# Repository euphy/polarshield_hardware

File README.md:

Polarshield Hardware
====================

This is the source for the Polarshield hardware, in EAGLE format.  
I have also included the last set of generated Gerber files that were used to make
the most recent batch of PCBs. These can be purchased through polargraph.bigcartel.com.

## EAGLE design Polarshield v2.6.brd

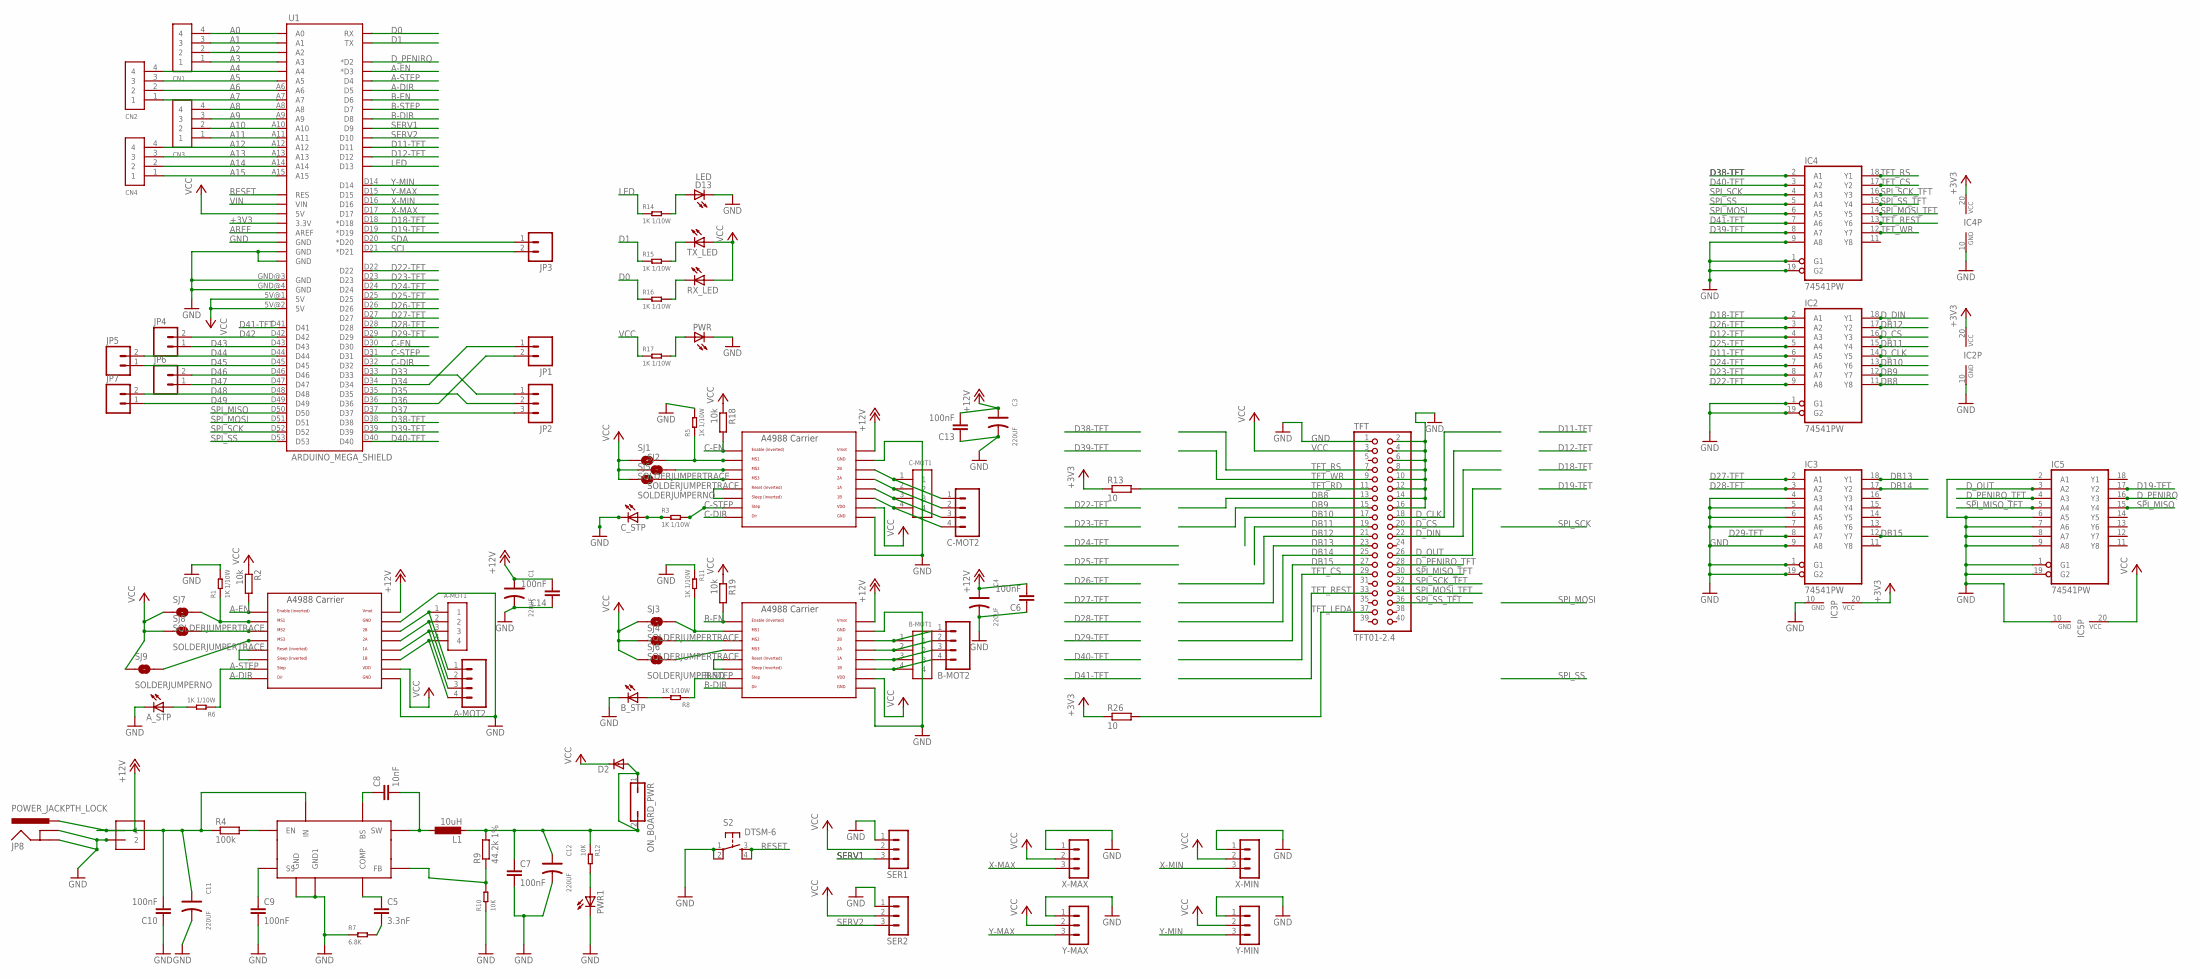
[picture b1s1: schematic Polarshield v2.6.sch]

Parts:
A-MOT1: 1X4-BIG; 1X04-BIG
A-MOT2: M04SCREW; SCREWTERMINAL-3.5MM-4
A_STP: LEDCHIP-LED0805; CHIP-LED0805
B-MOT1: 1X4-BIG; 1X04-BIG
B-MOT2: M04SCREW; SCREWTERMINAL-3.5MM-4
B_STP: LEDCHIP-LED0805; CHIP-LED0805
C1, C3, C4, C11, C12: 220UF; ELECTRO-SMD-C-6MM
C5: 3.3nF; C0402K
C6, C7, C9, C10, C13, C14: 100nF; C0402K
C8: 10nF; C0402K
C-MOT1: 1X4-BIG; 1X04-BIG
C-MOT2: M04SCREW; SCREWTERMINAL-3.5MM-4
CN1, CN2, CN3, CN4: 1X4-CLEANBIG; 1X04-CLEANBIG
C_STP: LEDCHIP-LED0805; CHIP-LED0805
D2: DIODE-DO214BA; DO214BA
D13: LED; CHIP-LED0805
IC1: MP2307; SOIC8
IC2, IC3, IC4, IC5: 74541PW; TSSOP20
J1: 1X2-3.5MM
JP1, JP3, JP4, JP5, JP6, JP7: M021X02_NO_SILK; 1X02_NO_SILK
JP2: M031X03_NO_SILK; 1X03_NO_SILK
JP8: POWER_JACKPTH_LOCK; POWER_JACK_PTH_LOCK
L1: 10uH; PIS2816
ON_BOARD_PWR: JP1Q; JP1
PWR, PWR1: LEDCHIP-LED0805; CHIP-LED0805
R1, R3, R5, R6, R8, R11, R14, R15, R16, R17: 1K 1/10W; R0603
R2, R18, R19: 10k; R0402
R4: 100k; R0603
R7: 6.8K; R0603
R9: 44.2k 1%; R0603
R10: 10K; R0805
R12: 10K; R0603
R13, R26: 10; R0603
RX_LED: LEDCHIP-LED0805; CHIP-LED0805
S2: DTSM-6
SER1, SER2: 3PIN-HEADER
SJ1, SJ2, SJ3, SJ4, SJ7, SJ8: SOLDERJUMPERTRACE; SJ_2S-TRACE
SJ5, SJ6, SJ9: SOLDERJUMPERNO; SJ_2S-NO
TFT: TFT01-2.4
TX_LED: LEDCHIP-LED0805; CHIP-LED0805
U1: ARDUINO_MEGA_SHIELD
U$1, U$6, U$7: A4988BREAKOUT
X-MAX: 3PIN-HEADER
X-MIN: 3PIN-HEADER
Y-MAX: 3PIN-HEADER
Y-MIN: 3PIN-HEADER

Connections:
+3V3: IC2.20 (VCC), IC3.20 (VCC), IC4.20 (VCC), R13.1, R26.1, U1.3.3V
+12V: C1.+, C3.+, C4.+, C6.2, C10.2, C11.+, C13.2, C14.2, IC1.IN, J1.1, JP8.PWR, R4.1, U$1.VMOT, U$6.VMOT, U$7.VMOT
A0: CN1.4, U1.A0
A1: CN1.3, U1.A1
A2: CN1.2, U1.A2
A3: CN1.1, U1.A3
A4: CN2.4, U1.A4
A5: CN2.3, U1.A5
A6: CN2.2, U1.A6
A7: CN2.1, U1.A7
A8: CN3.4, U1.A8
A9: CN3.3, U1.A9
A10: CN3.2, U1.A10
A11: CN3.1, U1.A11
A12: CN4.4, U1.A12
A13: CN4.3, U1.A13
A14: CN4.2, U1.A14
A15: CN4.1, U1.A15
A-DIR: U1.D5, U$1.DIR
A-EN: R2.2, U1.D3 (*D3), U$1.EN
A-STEP: R6.1, U1.D4, U$1.STEP
AREF: U1.AREF
B-DIR: U1.D8, U$7.DIR
B-EN: R19.2, U1.D6, U$7.EN
B-STEP: R8.1, U1.D7, U$7.STEP
C-DIR: U1.D32, U$6.DIR
C-EN: R18.2, U1.D30, U$6.EN
C-STEP: R3.2, U1.D31, U$6.STEP
D0: R16.1, U1.RX
D1: R15.1, U1.TX
D11-TFT: IC2.6 (A5), U1.D11
D12-TFT: IC2.4 (A3), U1.D12
D18-TFT: IC2.2 (A1), U1.D18 (*D18)
D19-TFT: IC5.17 (Y2), U1.D19 (*D19)
D22-TFT: IC2.9 (A8), U1.D22
D23-TFT: IC2.8 (A7), U1.D23
D24-TFT: IC2.7 (A6), U1.D24
D25-TFT: IC2.5 (A4), U1.D25
D26-TFT: IC2.3 (A2), U1.D26
D27-TFT: IC3.2 (A1), U1.D27
D28-TFT: IC3.3 (A2), U1.D28
D29-TFT: IC3.8 (A7), U1.D29
D33: JP2.1, U1.D33
D34: JP1.1, U1.D34
D35: JP2.2, U1.D35
D36: JP1.2, U1.D36
D37: JP2.3, U1.D37
D38-TFT: IC4.2 (A1), U1.D38
D39-TFT: IC4.8 (A7), U1.D39
D40-TFT: IC4.3 (A2), U1.D40
D41-TFT: IC4.7 (A6), U1.D41
D42: JP4.2, U1.D42
D43: JP4.1, U1.D43
D44: JP5.2, U1.D44
D45: JP5.1, U1.D45
D46: JP6.2, U1.D46
D47: JP6.1, U1.D47
D48: JP7.2, U1.D48
D49: JP7.1, U1.D49
DB8: IC2.11 (Y8), TFT.13
DB9: IC2.12 (Y7), TFT.15
DB10: IC2.13 (Y6), TFT.17
DB11: IC2.15 (Y4), TFT.19
DB12: IC2.17 (Y2), TFT.21
DB13: IC3.18 (Y1), TFT.23
DB14: IC3.17 (Y2), TFT.25
DB15: IC3.12 (Y7), TFT.27
D_CLK: IC2.14 (Y5), TFT.18
D_CS: IC2.16 (Y3), TFT.20
D_DIN: IC2.18 (Y1), TFT.22
D_OUT: IC5.3 (A2), TFT.26
D_PENIRQ: IC5.16 (Y3), U1.D2 (*D2)
D_PENIRQ_TFT: IC5.4 (A3), TFT.28
GND: A_STP.C, B_STP.C, C1.-, C3.-, C4.-, C6.1, C7.2, C9.2, C10.1, C11.-, C12.-, C13.1, C14.1, C_STP.C, D13.C, IC1.GND, IC1.GND1, IC2.1 (G1), IC2.10 (GND), IC2.19 (G2), IC3.1 (G1), IC3.4 (A3), IC3.5 (A4), IC3.6 (A5), IC3.7 (A6), IC3.9 (A8), IC3.10 (GND), IC3.19 (G2), IC4.1 (G1), IC4.9 (A8), IC4.10 (GND), IC4.19 (G2), IC5.1 (G1), IC5.2 (A1), IC5.6 (A5), IC5.7 (A6), IC5.8 (A7), IC5.9 (A8), IC5.10 (GND), IC5.19 (G2), J1.2, JP8.GND, JP8.GNDBREAK, PWR.C, PWR1.C, R1.2, R5.2, R7.1, R10.1, R11.1, S2.1, S2.2, SER1.1, SER2.1, TFT.1, TFT.2, TFT.4, TFT.6, TFT.8, TFT.10, TFT.12, TFT.14, TFT.16, U1.GND@0 (GND), U1.GND@1 (GND), U1.GND@2 (GND), U1.GND@3 (GND), U1.GND@4 (GND), U$1.GND, U$1.GND@0 (GND), U$6.GND, U$6.GND@0 (GND), U$7.GND, U$7.GND@0 (GND), X-MAX.1, X-MIN.1, Y-MAX.1, Y-MIN.1
LED: R14.1, U1.D13
unnamed: U$6.RST, U$6.SLP (SLEEP)
unnamed: PWR.A, R17.2
unnamed: R5.1, SJ1.2, U$6.MS1
unnamed: A-MOT1.1, A-MOT2.1, U$1.2B
unnamed: A-MOT1.2, A-MOT2.2, U$1.2A
unnamed: A-MOT1.3, A-MOT2.3, U$1.1A
unnamed: A-MOT1.4, A-MOT2.4, U$1.1B
unnamed: U$1.RST, U$1.SLP (SLEEP)
unnamed: R1.1, SJ7.2, U$1.MS1
unnamed: SJ2.2, U$6.MS2
unnamed: SJ8.2, U$1.MS2
unnamed: SJ5.2, U$6.MS3
unnamed: U$7.RST, U$7.SLP (SLEEP)
unnamed: SJ9.2, U$1.MS3
unnamed: R16.2, RX_LED.C
unnamed: R15.2, TX_LED.C
unnamed: SJ4.2, U$7.MS2
unnamed: B_STP.A, R8.2
unnamed: A_STP.A, R6.2
unnamed: D13.A, R14.2
unnamed: C-MOT1.1, C-MOT2.1, U$6.2B
unnamed: C-MOT1.2, C-MOT2.2, U$6.2A
unnamed: C_STP.A, R3.1
unnamed: C7.1, C12.+, D2.A, L1.2, ON_BOARD_PWR.1, ON_BOARD_PWR.2, R9.2, R12.1
unnamed: PWR1.A, R12.2
unnamed: C-MOT1.3, C-MOT2.3, U$6.1A
unnamed: C-MOT1.4, C-MOT2.4, U$6.1B
unnamed: B-MOT1.1, B-MOT2.1, U$7.2B
unnamed: B-MOT1.2, B-MOT2.2, U$7.2A
unnamed: B-MOT1.3, B-MOT2.3, U$7.1A
unnamed: SJ6.2, U$7.MS3
unnamed: IC1.FB, R9.1, R10.2
unnamed: R11.2, SJ3.2, U$7.MS1
unnamed: IC1.EN, R4.2
unnamed: B-MOT1.4, B-MOT2.4, U$7.1B
unnamed: C9.1, IC1.SS
unnamed: C5.2, R7.2
unnamed: C5.1, IC1.COMP
unnamed: C8.1, IC1.BS
unnamed: C8.2, IC1.SW, L1.1
RESET: S2.3, S2.4, U1.RES
SCL: JP3.2, U1.D21 (*D21)
SDA: JP3.1, U1.D20 (*D20)
SERV1: SER1.3, U1.D9
SERV2: SER2.3, U1.D10
SPI_MISO: IC5.15 (Y4), U1.D50
SPI_MISO_TFT: IC5.5 (A4), TFT.30
SPI_MOSI: IC4.6 (A5), U1.D51
SPI_MOSI_TFT: IC4.14 (Y5), TFT.34
SPI_SCK: IC4.4 (A3), U1.D52
SPI_SCK_TFT: IC4.16 (Y3), TFT.32
SPI_SS: IC4.5 (A4), U1.D53
SPI_SS_TFT: IC4.15 (Y4), TFT.36
TFT_CS: IC4.17 (Y2), TFT.29
TFT_LEDA: R26.2, TFT.37
TFT_RD: R13.2, TFT.11
TFT_REST: IC4.13 (Y6), TFT.33
TFT_RS: IC4.18 (Y1), TFT.7
TFT_WR: IC4.12 (Y7), TFT.9
VCC: D2.C, IC5.20 (VCC), R2.1, R17.1, R18.1, R19.1, RX_LED.A, SER1.2, SER2.2, SJ1.1, SJ2.1, SJ3.1, SJ4.1, SJ5.1, SJ6.1, SJ7.1, SJ8.1, SJ9.1, TFT.3, TX_LED.A, U1.5V@0 (5V), U1.5V@1 (5V), U1.5V@2 (5V), U$1.VDD, U$6.VDD, U$7.VDD, X-MAX.2, X-MIN.2, Y-MAX.2, Y-MIN.2
VIN: U1.VIN
X-MAX: U1.D17, X-MAX.3
X-MIN: U1.D16, X-MIN.3
Y-MAX: U1.D15, Y-MAX.3
Y-MIN: U1.D14, Y-MIN.3

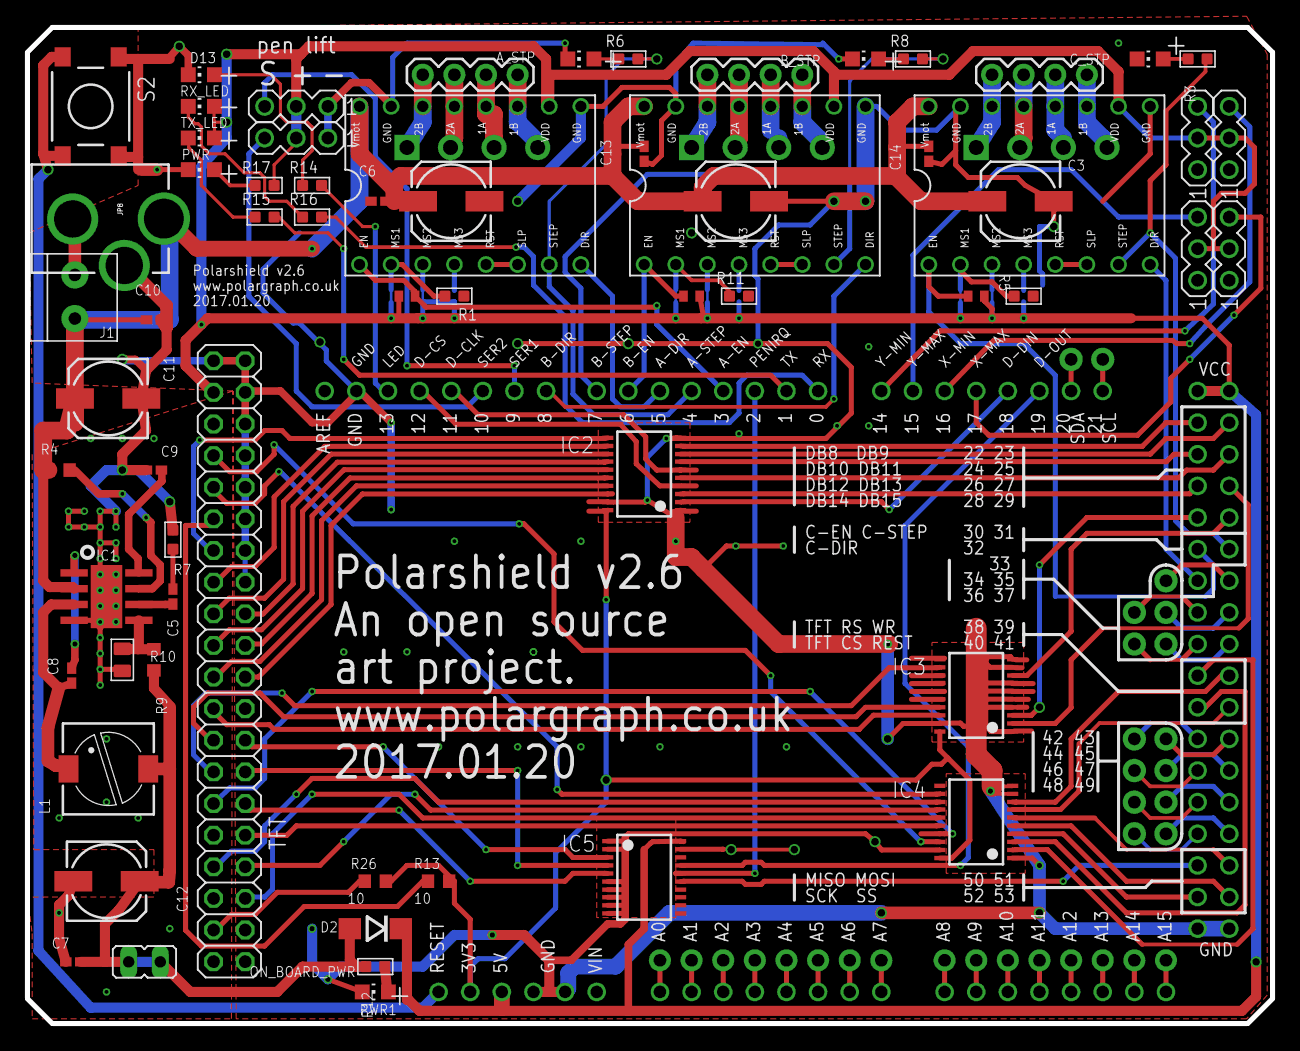
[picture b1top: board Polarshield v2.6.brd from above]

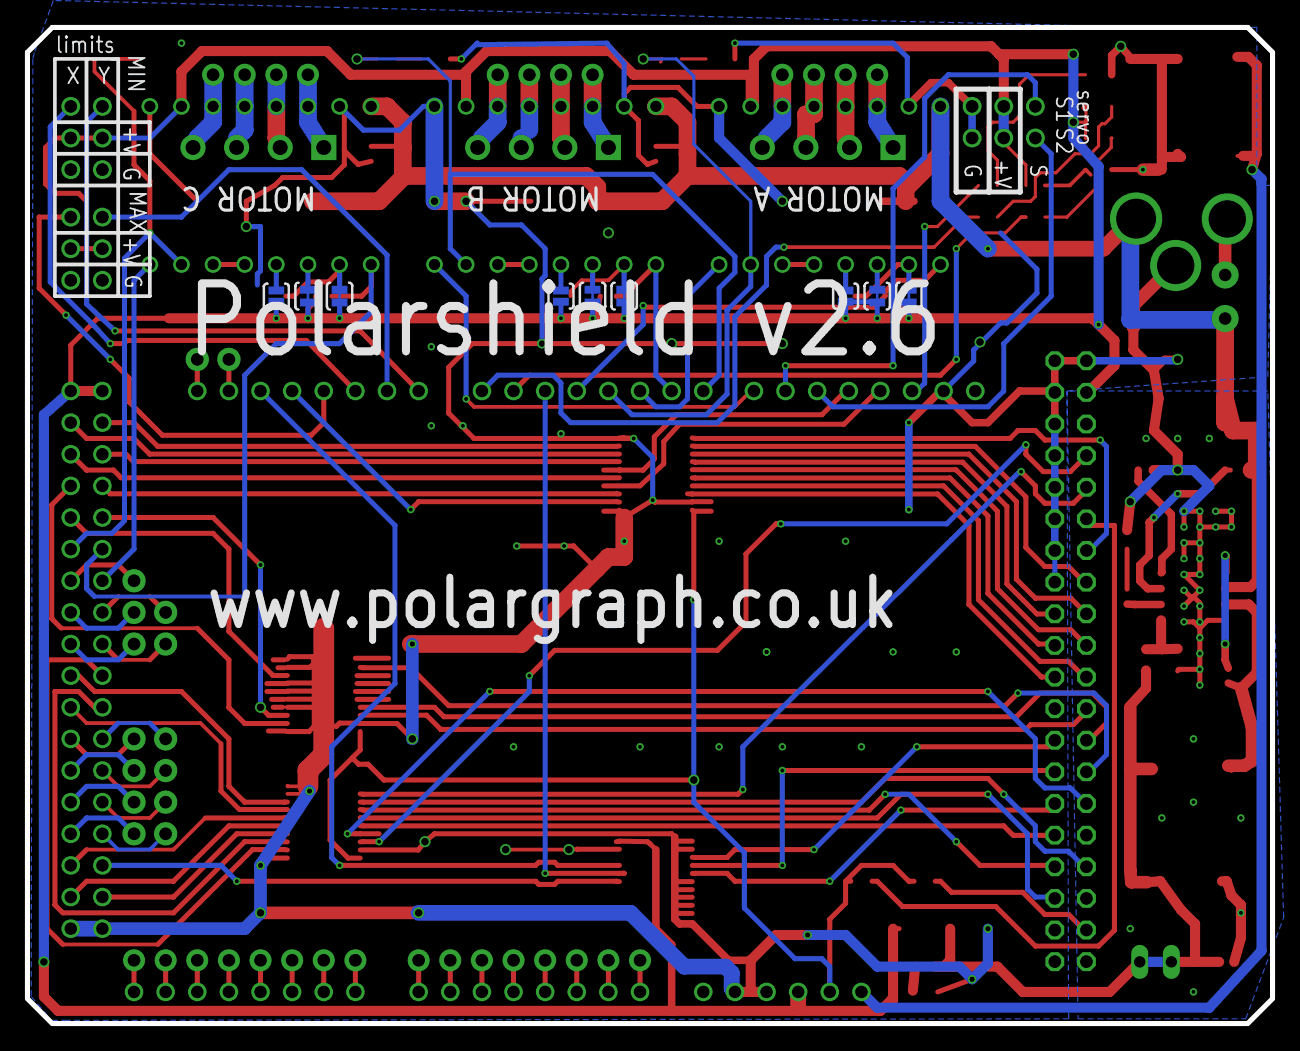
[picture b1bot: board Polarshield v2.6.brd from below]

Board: 4 copper layers, 100.0 x 80.0 mm, 89 parts (9 on the bottom side), 138 nets.

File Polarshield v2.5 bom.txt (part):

Partlist exported from C:/Users/sandy_000/OneDrive/Documents/eagle/Polarshield/Polarshield v2.5.sch at 09/12/2016 22:08:11

Part         Value               Device              Package               Description                           MF MPN OC_FARNELL OC_NEWARK PROD_ID    SF_ID    
A-MOT1                           1X4-BIG             1X04-BIG              4-pin connector                                                                       
A-MOT2                           M04SCREW            SCREWTERMINAL-3.5MM-4 Header 4                                                                              
A_STP                            LEDCHIP-LED0805     CHIP-LED0805          LED                                                                                   
B-MOT1                           1X4-BIG             1X04-BIG              4-pin connector                                                                       
B-MOT2                           M04SCREW            SCREWTERMINAL-3.5MM-4 Header 4                                                                              
B_STP                            LEDCHIP-LED0805     CHIP-LED0805          LED                                                                                   
C-MOT1                           1X4-BIG             1X04-BIG              4-pin connector                                                                       
C-MOT2                           M04SCREW            SCREWTERMINAL-3.5MM-4 Header 4                                                                              
C1           100uF               CPOL-EU153CLV-0605  153CLV-0605           POLARIZED CAPACITOR, European symbol                                                  
C3           100uF               CPOL-EU153CLV-0605  153CLV-0605           POLARIZED CAPACITOR, European symbol                                                  
C4           100uF               CPOL-EU153CLV-0605  153CLV-0605           POLARIZED CAPACITOR, European symbol                                                  
C5           3.3nF               C-EUC0805K          C0805K                CAPACITOR, European symbol                                                            
C6           100nF               C-EUC0805           C0805                 CAPACITOR, European symbol                                                            
C7           100nF               C-EUC0805K          C0805K                CAPACITOR, European symbol                                                            
C8           10nF                C-EUC0805K          C0805K                CAPACITOR, European symbol                                                            
C9           100nF               C-EUC0805K          C0805K                CAPACITOR, European symbol                                                            
C10          100nF               C-EUC0805K          C0805K                CAPACITOR, European symbol                                                            
C11          220uF               CPOL-EU153CLV-0807  153CLV-0807           POLARIZED CAPACITOR, European symbol                                                  
C12          220uF               CPOL-EU153CLV-0807  153CLV-0807           POLARIZED CAPACITOR, European symbol                                                  
C13          100nF               C-EUC0805           C0805                 CAPACITOR, European symbol                                                            
C14          100nF               C-EUC0805           C0805                 CAPACITOR, European symbol                                                            
CN1                              1X4-CLEANBIG        1X04-CLEANBIG         4-pin connector                                                                       
CN2                              1X4-CLEANBIG        1X04-CLEANBIG         4-pin connector                                                                       
CN3                              1X4-CLEANBIG        1X04-CLEANBIG         4-pin connector                                                                       
CN4                              1X4-CLEANBIG        1X04-CLEANBIG         4-pin connector                                                                       
C_STP                            LEDCHIP-LED0805     CHIP-LED0805          LED                                                                                   
D2                               DIODE-DO214BA       DO214BA               DIODE                                                                                 
D13          LED                 LEDCHIP-LED0805     CHIP-LED0805          LED                                                                                   
IC1          MP2307              MP2307              SOIC8                                                                                                       
IC2          74541PW             74541PW             TSSOP20               Octal BUFFER and LINE DRIVER, 3-state                                                 
IC3          74541PW             74541PW             TSSOP20               Octal BUFFER and LINE DRIVER, 3-state                                                 
IC4          74541PW             74541PW             TSSOP20               Octal BUFFER and LINE DRIVER, 3-state                                                 
IC5          74541PW             74541PW             TSSOP20               Octal BUFFER and LINE DRIVER, 3-state                                                 
J1           1X2-3.5MM           1X2-3.5MM           1X2-3.5MM             3.5mm Terminal block                                                                  
JP1                              M021X02_NO_SILK     1X02_NO_SILK          Standard 2-pin 0.1" header. Use with                                                  
JP2                              M031X03_NO_SILK     1X03_NO_SILK          Header 3                                                                              
JP3                              M021X02_NO_SILK     1X02_NO_SILK          Standard 2-pin 0.1" header. Use with                                                  
JP4                              M021X02_NO_SILK     1X02_NO_SILK          Standard 2-pin 0.1" header. Use with                                                  
JP5                              M021X02_NO_SILK     1X02_NO_SILK          Standard 2-pin 0.1" header. Use with                                                  
JP6                              M021X02_NO_SILK     1X02_NO_SILK          Standard 2-pin 0.1" header. Use with                                                  
JP7                              M021X02_NO_SILK     1X02_NO_SILK          Standard 2-pin 0.1" header. Use with                                                  
JP8          POWER_JACKPTH_LOCK  POWER_JACKPTH_LOCK  POWER_JACK_PTH_LOCK   Power Jack                                                        CONN-08197 PRT-00119
L1           10uH                L-EUPIS2816         PIS2816               INDUCTOR, European symbol                                                             
ON_BOARD_PWR                     JP1Q                JP1                   JUMPER                                                                                
PWR                              LEDCHIP-LED0805     CHIP-LED0805          LED                                                                                   
PWR1                             LEDCHIP-LED0805     CHIP-LED0805          LED                                                                                   
R2           10k                 R-EU_R0805          R0805                 RESISTOR, European symbol                                                             
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
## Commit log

2013-08-28 Init upload of polarshield board files
2013-08-28 swapped motor A, C. Moved servo and endstops.
2013-08-31 Added some LEDs for rx, tx and step
2013-08-31 Finished v1.5 and sent off to be made.
2013-09-13 Added fixed v1.5. Cosmetic only, but rezipped because I messed up the file upload and THESE BOARDS ARE WORTHLESS!! Well I have fixed and reuploaded. This is functionally identical, so no version incr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
2013-10-18 Merged a resistor into a network and changed a few values, also cleaned up silkscreen.
2013-11-26 Added dxf that I used for the screen printing.
2013-11-26 Removed a load of old versions.
2014-01-29 Couple updates.
2014-01-29 Revert "Removed a load of old versions."
    This reverts commit 932d87ee5b56b293ae88f7cca643fe68918375a7.
2014-02-03 Revert "Revert "Removed a load of old versions.""
    This reverts commit 689725b0dcb57211e49b9427af1c8fa31b99f5e5.
2014-04-29 Files as sent to board mfr 29.04.2014.
2014-05-12 v2.0 really
    First attempt.
2014-06-07 2.0c
2014-06-08 v2c that has gone to the PCB makers last night.
2014-06-08 Version 2.0d
2014-07-31 v2.0d
2014-08-08 Got rid of some old files.
2015-04-18 Updated polarshield to v2.1
2015-04-18 Ran the DRU, ready for making.
2015-11-19 Updated to v2.2a: Made a couple holes smaller, rebuilt gerbers properly.
2016-02-18 Added v2.3
2016-04-04 v2.1
2016-04-04 v2.2 (missing silkscreen)
2016-04-04 v2.2.1 aka v2.2a - added missing silkscreen
2016-04-04 v2.4
2016-04-04 Removing old versions
2017-02-12 Polarshield 2.5 gerbers and source
2017-02-12 Added 2.6
2017-02-12 Removing v2.4
2017-06-26 Made sch more readable
2017-06-26 Some renders of v2.5

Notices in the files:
parts and their libraries:
SparkFun-Connectors: Licensing: Creative Commons ShareAlike 4.0 International - https://creativecommons.org/licenses/by-sa/4.0
